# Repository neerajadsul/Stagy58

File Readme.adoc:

= Ortho82Split Keyboard
This is the current design iteration which has 41 keys on each half in orthogonal matrix.

KiCAD 7 Render

image::images/Ortho82SplitLeftHalf.jpg[]

Fully assembled two halves of the keyboard, side by side

image::images/FullyAssembledLeftRight.jpg[]

== Programmers Model

=== Row Signals to Microcontroller Pin

[cols="1,1,1"]
|===
| Signal | Pin | Keyboard Row

|ROW_F | PD0 | Esc, Function row
|ROW_0 | PD1 | Backtick, Numbers row
|ROW_1 | PD2 | Tab, QWERTY row
|ROW_2 | PD3 | Caps, ASDFG row
|ROW_3 | PD4 | Shift, ZXCVB row
|ROW_4 | PD5 | Ctrl, Fn, Opt, Cmd, Space row
|===

=== Column Signals to Microcontroller Pin
==== Left Half of the Split Keyboard
[cols="s,1,1,1,1,1,1,1"]
|===
|Signal | COL_0 | COL_1  | COL_2 | COL_3 | COL_4 | COL_5  | COL_6

| Pin | PC0 | PC1 | PC2 | PC3 | PC4 | PC5 | PC6 

|ROW_F | Esc | F1 | F2 | F3 | F4 | F5 | F6
|ROW_0 | ` (backtick) | 1 | 2 | 3 | 4 | 5 | 6
|ROW_1 | Tab | Q | W | E | R | T | Y
|ROW_2 | Caps | A | S | D | F | G | H
|ROW_3 | Shift | \ (backslash) | Z | X | C | V | B 
|ROW_4 | <NO KEY> | Ctrl  | MOD | Fn | Option | Cmd | Space | 
|===

==== Right Half of the Split Keyboard
[cols="s,1,1,1,1,1,1,1"]
|===
| Signal | COL_6 | COL_5  | COL_4 | COL_3 | COL_2 | COL_1  | COL_0
| Pin | PC6 | PC5 | PC4 | PC3 | PC2 | PC1 | PC0 

|ROW_F | F7 | F8 | F9 | F10 | F11 | F12 | Del
|ROW_0 | 7 | 8 | 9 | 0 | - | = | Backspace
|ROW_1 | U | I | O | P | [ | ] | Enter
|ROW_2 | J | K | L | ;: | '@ (quote) | # | Enter
|ROW_3 | N | M | ,< | .> | /? | UP | SHIFT 
|ROW_4 | Space | Cmd  | Option | LEFT | DOWN | RIGHT | <No Key> | 
|===

=== Communication between Left and Right Halves
Two halves of the split keyboard are connected by USART connection.
[cols="s,1,1"]
|===
| Signal | RXD0 | TXD0
| Pin | PE2 | PE3 
|===

=== Left/Right Half Identification and Indicator LED
Left and right are identified by setting a solder jumper on the board.
Left is 0 and right is 1.

[cols="s,1,1"]
|===
| Signal | Left-Right | Indicator LED
| Pin | PB2 | PB3 
|===

== Iterative Design History
I started with my TKL (tenkeyless) keyboard and tried to reduce the keys. 
I managed to reduce to 60 = 58 main + 2 extended keys for the keyboard.
This was partially inspired by Lily58 and other 60% keyboards avaialble. 
Also Kyria keyboard inspired me to customise the positions of the keys 
adapted to my hands and fingers. 
Following ficgure shows how I came up with draft with reduction in keys 
and logical positions in a worksheet. 

image::images/keys_reduction.png[]

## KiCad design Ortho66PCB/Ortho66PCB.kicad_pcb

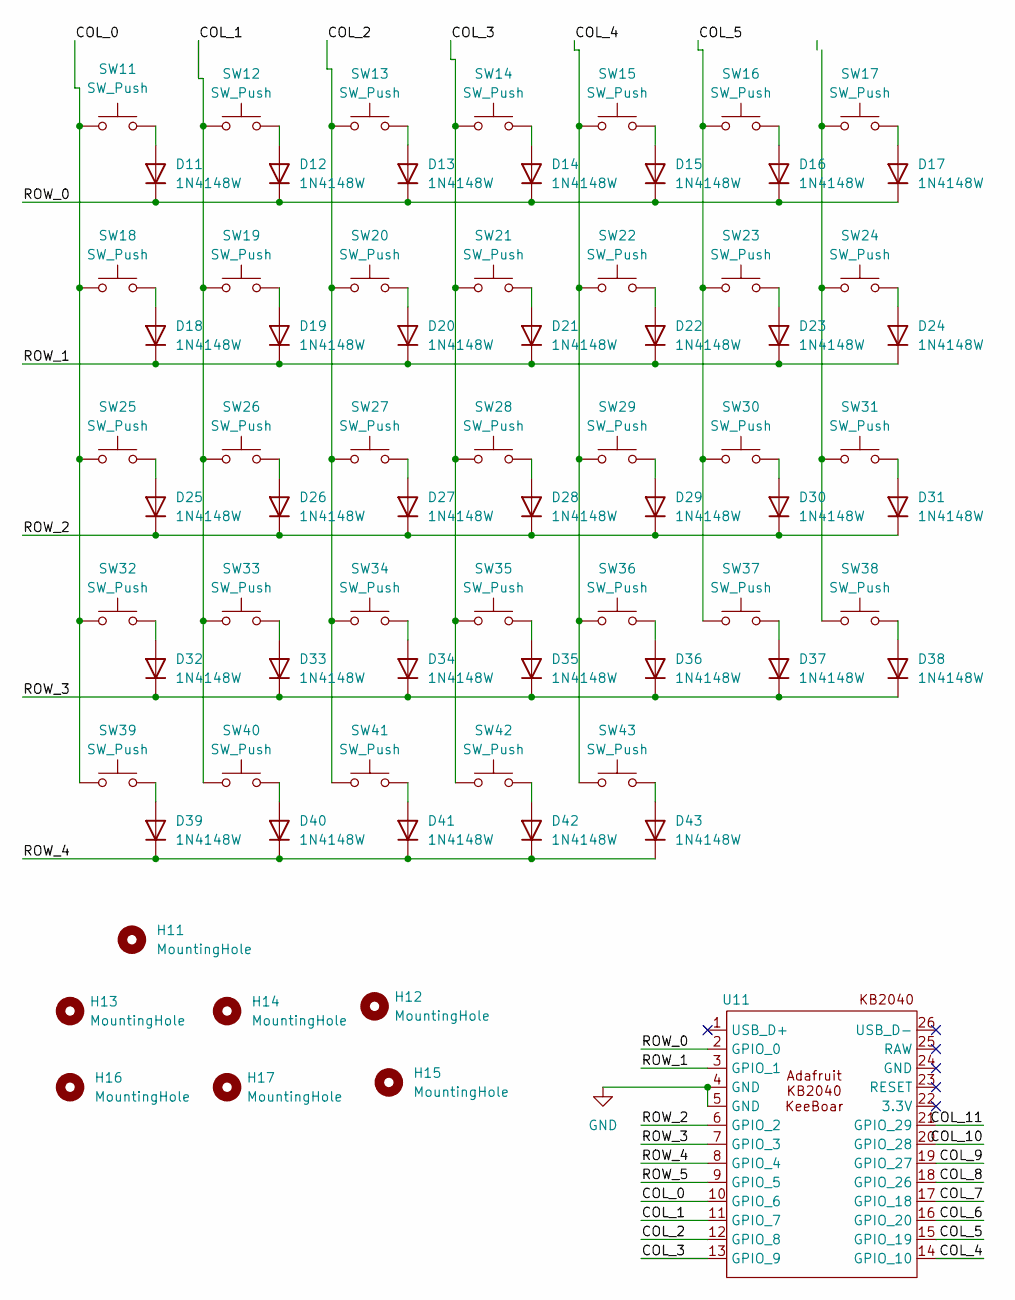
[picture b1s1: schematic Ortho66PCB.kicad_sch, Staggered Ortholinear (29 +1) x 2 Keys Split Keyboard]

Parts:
D11, D12, D13, D14, D15, D16, D17, D18, D19, D20, D21, D22, D23, D24, D25, D26, D27, D28, D29, D30, D31, D32, D33, D34, D35, D36, D37, D38, D39, D40, D41, D42, D43: 1N4148W; D_SOD-123
H11: MountingHole; MountingHole_2.7mm_M2.5
H12, H13, H14, H15, H16, H17: MountingHole; MountingHole_3.2mm_M3
SW11, SW18, SW25, SW32: SW_Push; SW_Kailh_Choc_V1V2_1.50u
SW12, SW13, SW14, SW15, SW16, SW17, SW19, SW20, SW21, SW22, SW23, SW24, SW26, SW27, SW28, SW29, SW30, SW31, SW33, SW34, SW35, SW36, SW37, SW38, SW39, SW40, SW42, SW43: SW_Push; SW_Kailh_Choc_V1V2_1.00u
SW41: SW_Push; SW_Kailh_Choc_V1V2_2.00u
U11: KB2040

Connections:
/COL_0: SW11.1, SW18.1, SW25.1, SW32.1, SW39.1, U11.10 (GPIO_6)
/COL_1: SW12.1, SW19.1, SW26.1, SW33.1, SW40.1, U11.11 (GPIO_7)
/COL_2: SW13.1, SW20.1, SW27.1, SW34.1, SW41.1, U11.12 (GPIO_8)
/COL_3: SW14.1, SW21.1, SW28.1, SW35.1, SW42.1, U11.13 (GPIO_9)
/COL_4: SW15.1, SW22.1, SW29.1, SW36.1, SW43.1, U11.14 (GPIO_10)
/COL_5: SW16.1, SW23.1, SW30.1, SW37.1, U11.15 (GPIO_19)
/COL_6: U11.16 (GPIO_20)
/COL_7: U11.17 (GPIO_18)
/COL_8: U11.18 (GPIO_26)
/COL_9: U11.19 (GPIO_27)
/COL_10: U11.20 (GPIO_28)
/COL_11: U11.21 (GPIO_29)
/ROW_0: D11.1 (K), D12.1 (K), D13.1 (K), D14.1 (K), D15.1 (K), D16.1 (K), D17.1 (K), U11.2 (GPIO_0)
/ROW_1: D18.1 (K), D19.1 (K), D20.1 (K), D21.1 (K), D22.1 (K), D23.1 (K), D24.1 (K), U11.3 (GPIO_1)
/ROW_2: D25.1 (K), D26.1 (K), D27.1 (K), D28.1 (K), D29.1 (K), D30.1 (K), D31.1 (K), U11.6 (GPIO_2)
/ROW_3: D32.1 (K), D33.1 (K), D34.1 (K), D35.1 (K), D36.1 (K), D37.1 (K), D38.1 (K), U11.7 (GPIO_3)
/ROW_4: D39.1 (K), D40.1 (K), D41.1 (K), D42.1 (K), D43.1 (K), U11.8 (GPIO_4)
/ROW_5: U11.9 (GPIO_5)
GND: U11.4 (GND), U11.5 (GND)
unnamed: D11.2 (A), SW11.2
unnamed: D12.2 (A), SW12.2
unnamed: D13.2 (A), SW13.2
unnamed: D14.2 (A), SW14.2
unnamed: D15.2 (A), SW15.2
unnamed: D16.2 (A), SW16.2
unnamed: D17.2 (A), SW17.2
unnamed: D18.2 (A), SW18.2
unnamed: D19.2 (A), SW19.2
unnamed: D20.2 (A), SW20.2
unnamed: D21.2 (A), SW21.2
unnamed: D22.2 (A), SW22.2
unnamed: D23.2 (A), SW23.2
unnamed: D24.2 (A), SW24.2
unnamed: D25.2 (A), SW25.2
unnamed: D26.2 (A), SW26.2
unnamed: D27.2 (A), SW27.2
unnamed: D28.2 (A), SW28.2
unnamed: D29.2 (A), SW29.2
unnamed: D30.2 (A), SW30.2
unnamed: D31.2 (A), SW31.2
unnamed: D32.2 (A), SW32.2
unnamed: D33.2 (A), SW33.2
unnamed: D34.2 (A), SW34.2
unnamed: D35.2 (A), SW35.2
unnamed: D36.2 (A), SW36.2
unnamed: D37.2 (A), SW37.2
unnamed: D38.2 (A), SW38.2
unnamed: D39.2 (A), SW39.2
unnamed: D40.2 (A), SW40.2
unnamed: D41.2 (A), SW41.2
unnamed: D42.2 (A), SW42.2
unnamed: D43.2 (A), SW43.2
unnamed: SW17.1, SW24.1, SW31.1, SW38.1

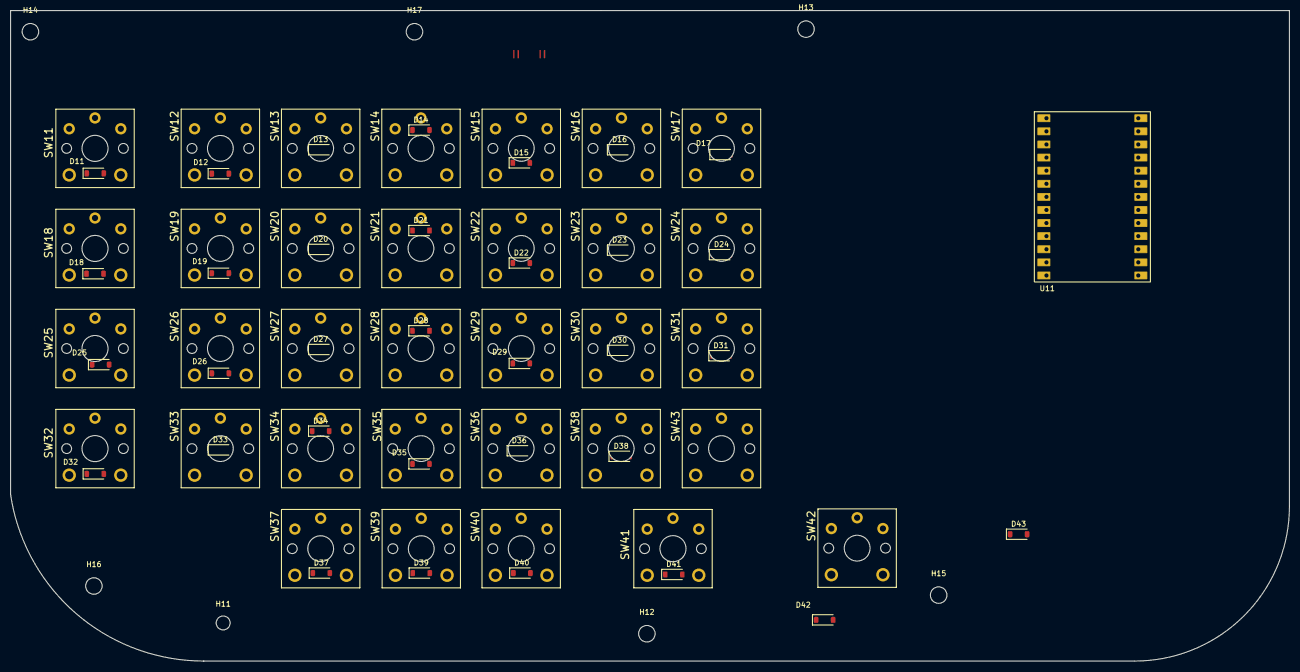
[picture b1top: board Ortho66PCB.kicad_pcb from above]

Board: 2 copper layers, 247.9 x 126.1 mm, 74 parts (0 on the bottom side), 46 nets.

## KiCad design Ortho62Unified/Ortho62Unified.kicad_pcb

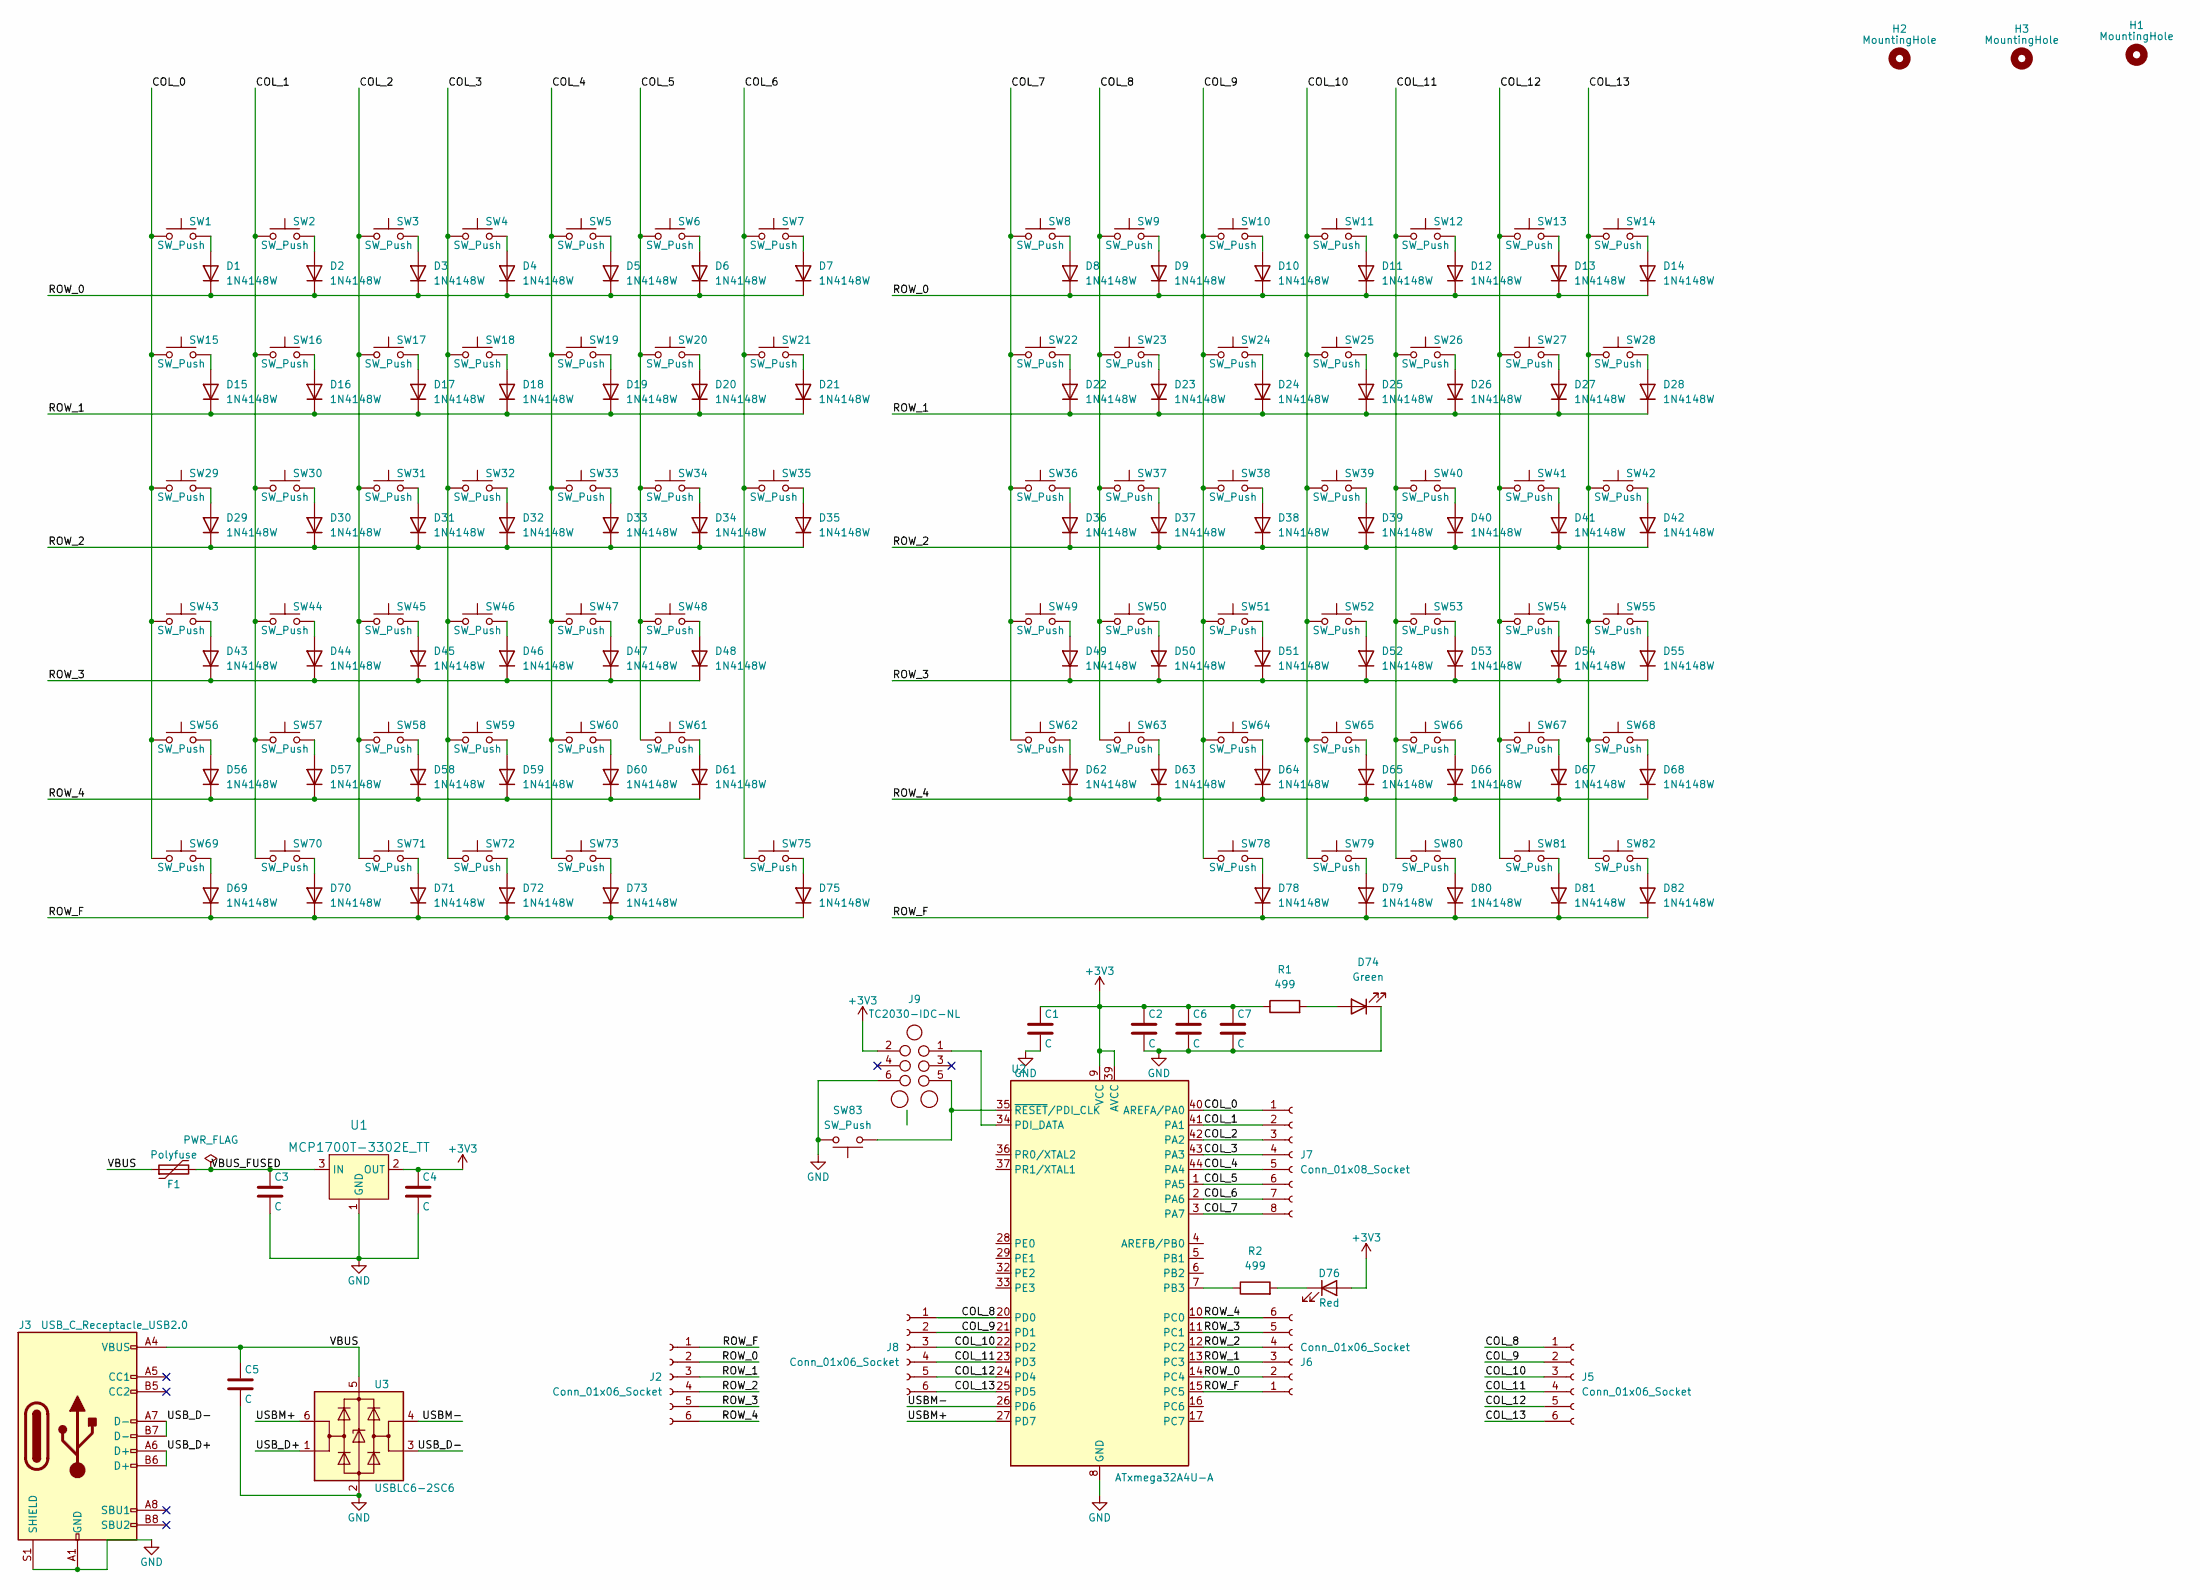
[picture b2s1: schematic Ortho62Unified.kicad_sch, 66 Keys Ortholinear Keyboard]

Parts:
C1, C2, C3, C4, C5, C6, C7: C; C_0603_1608Metric_Pad1.08x0.95mm_HandSolder
D1, D2, D3, D4, D5, D6, D7, D8, D9, D10, D11, D12, D13, D14, D15, D16, D17, D18, D19, D20, D21, D22, D23, D24, D25, D26, D27, D28, D29, D30, D31, D32, D33, D34, D35, D36, D37, D38, D39, D40, D41, D42, D43, D44, D45, D46, D47, D48, D49, D50, D51, D52, D53, D54, D55, D56, D57, D58, D59, D60, D61, D62, D63, D64, D65, D66, D67, D68, D69, D70, D71, D72, D73, D75, D78, D79, D80, D81, D82: 1N4148W; D_SOD-123
D74: Green; LED_0805_2012Metric_Pad1.15x1.40mm_HandSolder
D76: Red; LED_0805_2012Metric_Pad1.15x1.40mm_HandSolder
F1: Polyfuse; Fuse_1206_3216Metric_Pad1.42x1.75mm_HandSolder
H1, H2, H3: MountingHole; MountingHole_3.2mm_M3
J2, J5, J6, J8: Conn_01x06_Socket; PinHeader_1x06_P1.27mm_Vertical
J3: USB_C_Receptacle_USB2.0; USB_C_Receptacle_GCT_USB4085_HandSolder_SMT
J7: Conn_01x08_Socket; PinHeader_1x08_P1.27mm_Vertical
J9: TC2030-IDC-NL
R1: 499; R_0805_2012Metric_Pad1.20x1.40mm_HandSolder
R2: 499; LED_0805_2012Metric_Pad1.15x1.40mm_HandSolder
SW1, SW2, SW3, SW4, SW5, SW6, SW8, SW9, SW10, SW11, SW12, SW13, SW15, SW16, SW17, SW18, SW19, SW20, SW22, SW23, SW24, SW25, SW26, SW27, SW29, SW30, SW31, SW32, SW33, SW34, SW36, SW37, SW38, SW39, SW40, SW41, SW43, SW44, SW45, SW46, SW47, SW48, SW49, SW50, SW51, SW52, SW53, SW54, SW55, SW57, SW58, SW59, SW60, SW63, SW64, SW65, SW66, SW68, SW69, SW70, SW71, SW72, SW73, SW78, SW79, SW80, SW81: SW_Push; SW_Kailh_Choc_V1V2_1.00u
SW7, SW14, SW21, SW28, SW35, SW42, SW56, SW61, SW62, SW67, SW75, SW82: SW_Push; SW_Kailh_Choc_V1V2_1.50u
SW83: SW_Push; SW_Tactile_SPST_NO_Straight_CK_PTS636Sx25SMTRLFS
U1: MCP1700T-3302E_TT; SOT-23-3; MPN MCP1700T-3302E/TT; Digi-Key_PN MCP1700T3302ETTCT-ND
U2: ATxmega32A4U-A; TQFP-44_10x10mm_P0.8mm
U3: USBLC6-2SC6; SOT-23-6

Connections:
+3V3: C1.1, C2.1, C4.1, C6.1, C7.1, D76.2 (A), J9.2, R1.1, U1.2 (OUT), U2.9 (VCC), U2.19 (VCC), U2.31 (VCC), U2.39 (AVCC)
/COL_0: J7.1, SW1.1, SW15.1, SW29.1, SW43.1, SW56.1, SW69.1, U2.40 (AREFA/PA0)
/COL_1: J7.2, SW2.1, SW16.1, SW30.1, SW44.1, SW57.1, SW70.1, U2.41 (PA1)
/COL_2: J7.3, SW3.1, SW17.1, SW31.1, SW45.1, SW58.1, SW71.1, U2.42 (PA2)
/COL_3: J7.4, SW4.1, SW18.1, SW32.1, SW46.1, SW59.1, SW72.1, U2.43 (PA3)
/COL_4: J7.5, SW5.1, SW19.1, SW33.1, SW47.1, SW60.1, SW73.1, U2.44 (PA4)
/COL_5: J7.6, SW6.1, SW20.1, SW34.1, SW48.1, SW61.1, U2.1 (PA5)
/COL_6: J7.7, SW7.1, SW21.1, SW35.1, SW75.1, U2.2 (PA6)
/COL_7: J7.8, SW8.1, SW22.1, SW36.1, SW49.1, SW62.1, U2.3 (PA7)
/COL_8: J5.1, J8.1, SW9.1, SW23.1, SW37.1, SW50.1, SW63.1, U2.20 (PD0)
/COL_9: J5.2, J8.2, SW10.1, SW24.1, SW38.1, SW51.1, SW64.1, SW78.1, U2.21 (PD1)
/COL_10: J5.3, J8.3, SW11.1, SW25.1, SW39.1, SW52.1, SW65.1, SW79.1, U2.22 (PD2)
/COL_11: J5.4, J8.4, SW12.1, SW26.1, SW40.1, SW53.1, SW66.1, SW80.1, U2.23 (PD3)
/COL_12: J5.5, J8.5, SW13.1, SW27.1, SW41.1, SW54.1, SW67.1, SW81.1, U2.24 (PD4)
/COL_13: J5.6, J8.6, SW14.1, SW28.1, SW42.1, SW55.1, SW68.1, SW82.1, U2.25 (PD5)
/ROW_0: D1.1 (K), D2.1 (K), D3.1 (K), D4.1 (K), D5.1 (K), D6.1 (K), D7.1 (K), D8.1 (K), D9.1 (K), D10.1 (K), D11.1 (K), D12.1 (K), D13.1 (K), D14.1 (K), J2.2, J6.2, U2.14 (PC4)
/ROW_1: D15.1 (K), D16.1 (K), D17.1 (K), D18.1 (K), D19.1 (K), D20.1 (K), D21.1 (K), D22.1 (K), D23.1 (K), D24.1 (K), D25.1 (K), D26.1 (K), D27.1 (K), D28.1 (K), J2.3, J6.3, U2.13 (PC3)
/ROW_2: D29.1 (K), D30.1 (K), D31.1 (K), D32.1 (K), D33.1 (K), D34.1 (K), D35.1 (K), D36.1 (K), D37.1 (K), D38.1 (K), D39.1 (K), D40.1 (K), D41.1 (K), D42.1 (K), J2.4, J6.4, U2.12 (PC2)
/ROW_3: D43.1 (K), D44.1 (K), D45.1 (K), D46.1 (K), D47.1 (K), D48.1 (K), D49.1 (K), D50.1 (K), D51.1 (K), D52.1 (K), D53.1 (K), D54.1 (K), D55.1 (K), J2.5, J6.5, U2.11 (PC1)
/ROW_4: D56.1 (K), D57.1 (K), D58.1 (K), D59.1 (K), D60.1 (K), D61.1 (K), D62.1 (K), D63.1 (K), D64.1 (K), D65.1 (K), D66.1 (K), D67.1 (K), D68.1 (K), J2.6, J6.6, U2.10 (PC0)
/ROW_F: D69.1 (K), D70.1 (K), D71.1 (K), D72.1 (K), D73.1 (K), D75.1 (K), D78.1 (K), D79.1 (K), D80.1 (K), D81.1 (K), D82.1 (K), J2.1, J6.1, U2.15 (PC5)
/USBM+: U2.27 (PD7), U3.6 (I/O1)
/USBM-: U2.26 (PD6), U3.4 (I/O2)
/USB_D+: J3.A6 (D+), J3.B6 (D+), U3.1 (I/O1)
/USB_D-: J3.A7 (D-), J3.B7 (D-), U3.3 (I/O2)
/VBUS: C5.1, F1.1, J3.A4 (VBUS), J3.A9 (VBUS), J3.B4 (VBUS), J3.B9 (VBUS), U3.5 (VBUS)
/VBUS_FUSED: C3.1, F1.2, U1.3 (IN)
GND: C1.2, C2.2, C3.2, C4.2, C5.2, C6.2, C7.2, D74.1 (K), J3.A1 (GND), J3.A12 (GND), J3.B1 (GND), J3.B12 (GND), J3.S1 (SHIELD), J9.6, SW83.2, U1.1 (GND), U2.8 (GND), U2.18 (GND), U2.30 (GND), U2.38 (GND), U3.2 (GND)
unnamed: D1.2 (A), SW1.2
unnamed: D2.2 (A), SW2.2
unnamed: D3.2 (A), SW3.2
unnamed: D4.2 (A), SW4.2
unnamed: D5.2 (A), SW5.2
unnamed: D6.2 (A), SW6.2
unnamed: D7.2 (A), SW7.2
unnamed: D8.2 (A), SW8.2
unnamed: D9.2 (A), SW9.2
unnamed: D10.2 (A), SW10.2
unnamed: D11.2 (A), SW11.2
unnamed: D12.2 (A), SW12.2
unnamed: D13.2 (A), SW13.2
unnamed: D14.2 (A), SW14.2
unnamed: D15.2 (A), SW15.2
unnamed: D16.2 (A), SW16.2
unnamed: D17.2 (A), SW17.2
unnamed: D18.2 (A), SW18.2
unnamed: D19.2 (A), SW19.2
unnamed: D20.2 (A), SW20.2
unnamed: D21.2 (A), SW21.2
unnamed: D22.2 (A), SW22.2
unnamed: D23.2 (A), SW23.2
unnamed: D24.2 (A), SW24.2
unnamed: D25.2 (A), SW25.2
unnamed: D26.2 (A), SW26.2
unnamed: D27.2 (A), SW27.2
unnamed: D28.2 (A), SW28.2
unnamed: D29.2 (A), SW29.2
unnamed: D30.2 (A), SW30.2
unnamed: D31.2 (A), SW31.2
unnamed: D32.2 (A), SW32.2
unnamed: D33.2 (A), SW33.2
unnamed: D34.2 (A), SW34.2
unnamed: D35.2 (A), SW35.2
unnamed: D36.2 (A), SW36.2
unnamed: D37.2 (A), SW37.2
unnamed: D38.2 (A), SW38.2
unnamed: D39.2 (A), SW39.2
unnamed: D40.2 (A), SW40.2
unnamed: D41.2 (A), SW41.2
unnamed: D42.2 (A), SW42.2
unnamed: D43.2 (A), SW43.2
unnamed: D44.2 (A), SW44.2
unnamed: D45.2 (A), SW45.2
unnamed: D46.2 (A), SW46.2
unnamed: D47.2 (A), SW47.2
unnamed: D48.2 (A), SW48.2
unnamed: D49.2 (A), SW49.2
unnamed: D50.2 (A), SW50.2
unnamed: D51.2 (A), SW51.2
unnamed: D52.2 (A), SW52.2
unnamed: D53.2 (A), SW53.2
unnamed: D54.2 (A), SW54.2
unnamed: D55.2 (A), SW55.2
unnamed: D56.2 (A), SW56.2
unnamed: D57.2 (A), SW57.2
unnamed: D58.2 (A), SW58.2
unnamed: D59.2 (A), SW59.2
unnamed: D60.2 (A), SW60.2
unnamed: D61.2 (A), SW61.2
unnamed: D62.2 (A), SW62.2
unnamed: D63.2 (A), SW63.2
unnamed: D64.2 (A), SW64.2
unnamed: D65.2 (A), SW65.2
unnamed: D66.2 (A), SW66.2
unnamed: D67.2 (A), SW67.2
unnamed: D68.2 (A), SW68.2
unnamed: D69.2 (A), SW69.2
unnamed: D70.2 (A), SW70.2
unnamed: D71.2 (A), SW71.2
unnamed: D72.2 (A), SW72.2
unnamed: D73.2 (A), SW73.2
unnamed: D74.2 (A), R1.2
unnamed: D75.2 (A), SW75.2
unnamed: D76.1 (K), R2.2
unnamed: D78.2 (A), SW78.2
unnamed: D79.2 (A), SW79.2
unnamed: D80.2 (A), SW80.2
unnamed: D81.2 (A), SW81.2
unnamed: D82.2 (A), SW82.2
unnamed: J9.1, U2.34 (PDI_DATA)
unnamed: J9.5, SW83.1, U2.35 (~RESET/PDI_CLK)
unnamed: R2.1, U2.7 (PB3)

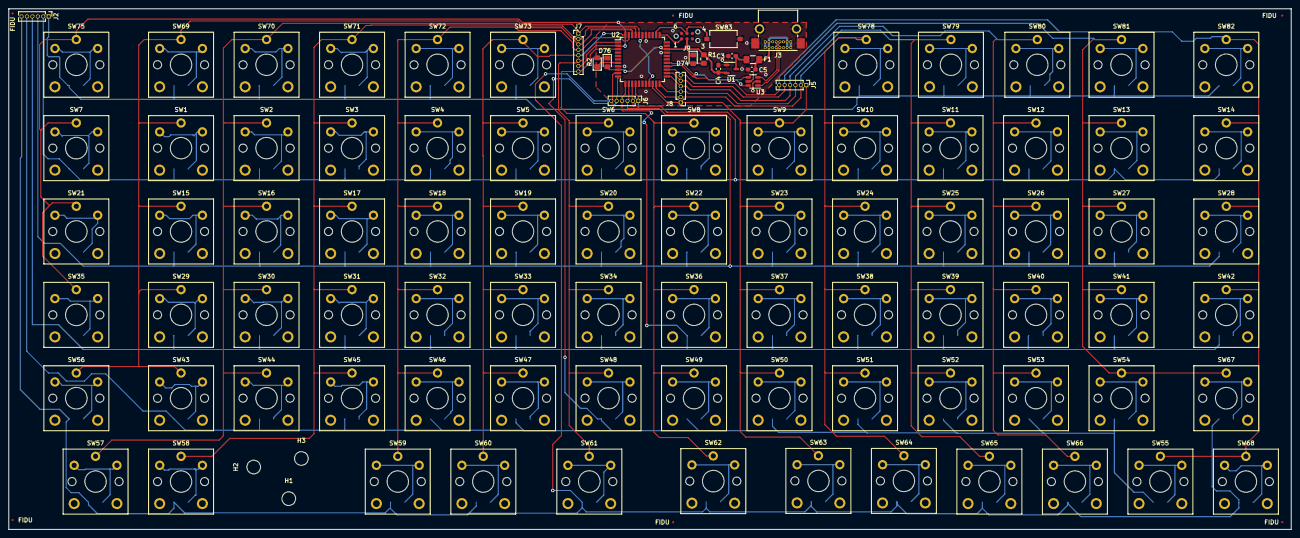
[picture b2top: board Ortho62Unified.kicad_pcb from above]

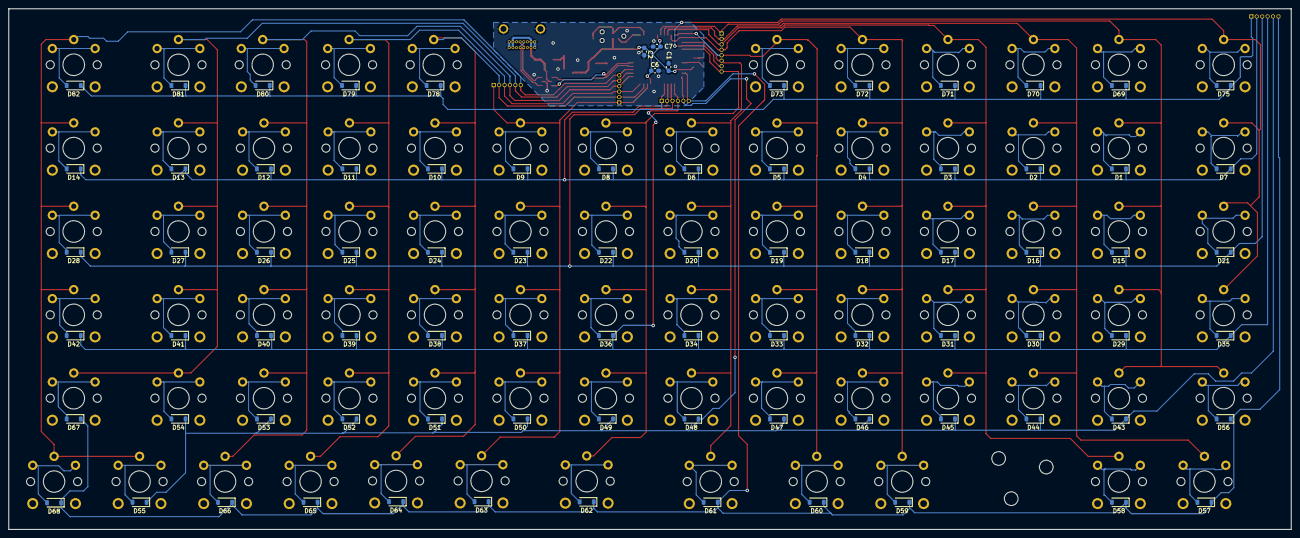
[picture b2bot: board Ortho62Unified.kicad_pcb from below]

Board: 2 copper layers, 300.0 x 121.8 mm, 190 parts (83 on the bottom side), 112 nets.

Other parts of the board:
FIDU: Fiducial_0.5mm_Mask1mm
FIDU#2, FIDU#3, FIDU#4, FIDU#5, FIDU#6: Fiducial_0.5mm_Mask1mm

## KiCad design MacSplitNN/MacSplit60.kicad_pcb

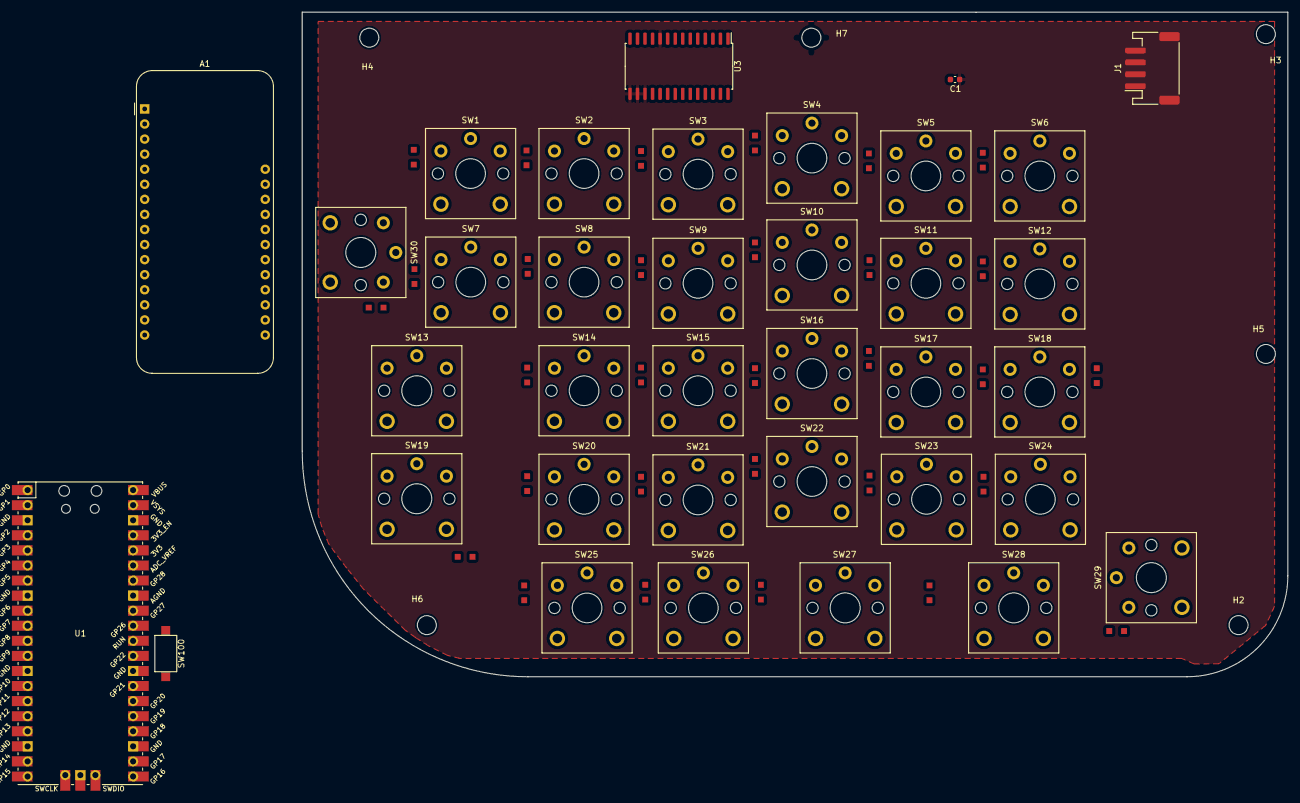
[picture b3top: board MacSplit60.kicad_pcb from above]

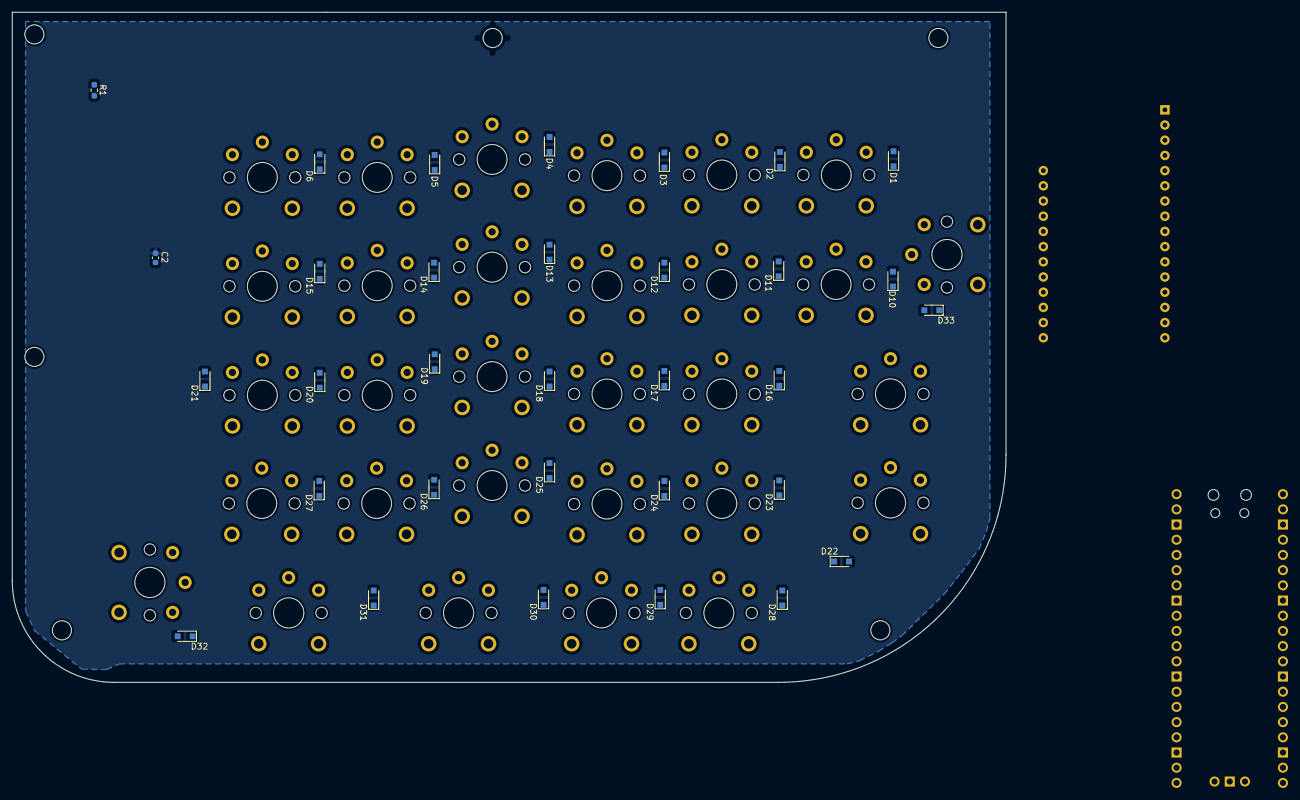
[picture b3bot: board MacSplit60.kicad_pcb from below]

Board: 2 copper layers, 166.1 x 112.0 mm, 74 parts (32 on the bottom side), 47 nets, no tracks yet.

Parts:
A1: Adafruit_Feather_Generic; Adafruit_Feather
C1, C2: C; C_0603_1608Metric
D1, D2, D3, D4, D5, D6, D10, D11, D12, D13, D14, D15, D16, D17, D18, D19, D20, D21, D22, D23, D24, D25, D26, D27, D28, D29, D30, D31, D32, D33: 1N4148W; D_SOD-323_Hand_Split_Keyboard
H2, H3, H4, H5, H6, H7: MountingHole; MountingHole_3.2mm_M3
J1: Conn_01x04_Pin; JST_PH_S4B-PH-SM4-TB_1x04-1MP_P2.00mm_Horizontal
R1: 0; R_0603_1608Metric_Pad0.98x0.95mm_HandSolder
SW1, SW2, SW3, SW4, SW5, SW6, SW7, SW8, SW9, SW10, SW11, SW12, SW14, SW15, SW16, SW17, SW18, SW20, SW21, SW22, SW23, SW24, SW25, SW26: SW_Push; SW_Kailh_Choc_V1V2_1.00u
SW13, SW19: SW_Push; SW_Kailh_Choc_V1V2_2.00u
SW27, SW28, SW29, SW30: SW_Push; SW_Kailh_Choc_V1V2_1.50u
SW100: SW_SPST; SW_SPST_CK_RS282G05A3
U1: Pico; RPi_Pico_SMD_TH
U3: MCP23017_SO; SOIC-28W_7.5x17.9mm_P1.27mm

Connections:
+VDC: C1.1, C2.1, J1.1, R1.2, U3.9 (VDD), U3.18 (~RESET)
/COL_0: SW1.1, SW7.1, SW13.1, SW19.1, SW25.1, U1.29 (GPIO22), U3.21 (GPA0)
/COL_1: SW2.1, SW8.1, SW14.1, SW20.1, SW26.1, U1.27 (GPIO21), U3.22 (GPA1)
/COL_2: SW3.1, SW9.1, SW15.1, SW21.1, SW27.1, U1.26 (GPIO20), U3.23 (GPA2)
/COL_3: SW4.1, SW10.1, SW16.1, SW22.1, SW28.1, U1.25 (GPIO19), U3.24 (GPA3)
/COL_4: SW5.1, SW11.1, SW17.1, SW23.1, SW29.1, U1.24 (GPIO18), U3.25 (GPA4)
/COL_5: SW6.1, SW12.1, SW18.1, SW24.1, SW30.1, U1.22 (GPIO17), U3.26 (GPA5)
/ROW_0: D1.1 (K), D2.1 (K), D3.1 (K), D4.1 (K), D5.1 (K), D6.1 (K), U1.21 (GPIO16), U3.1 (GPB0)
/ROW_1: D10.1 (K), D11.1 (K), D12.1 (K), D13.1 (K), D14.1 (K), D15.1 (K), U1.20 (GPIO15), U3.2 (GPB1)
/ROW_2: D16.1 (K), D17.1 (K), D18.1 (K), D19.1 (K), D20.1 (K), D21.1 (K), U1.19 (GPIO14), U3.3 (GPB2)
/ROW_3: D22.1 (K), D23.1 (K), D24.1 (K), D25.1 (K), D26.1 (K), D27.1 (K), U1.17 (GPIO13), U3.4 (GPB3)
/ROW_4: D28.1 (K), D29.1 (K), D30.1 (K), D31.1 (K), D32.1 (K), D33.1 (K), U1.16 (GPIO12), U3.5 (GPB4)
/SCL_IOEXP: J1.3, U1.5 (GPIO3), U3.12 (SCK)
/SDA_IOEXP: J1.2, U1.4 (GPIO2), U3.13 (SDA)
GND: C1.2, C2.2, J1.4, SW100.2 (B), U1.3 (GND), U1.8 (GND), U1.13 (GND), U1.18 (GND), U1.23 (GND), U1.28 (GND), U3.10 (VSS), U3.15 (A0), U3.16 (A1), U3.17 (A2)
unnamed: D1.2 (A), SW1.2
unnamed: D2.2 (A), SW2.2
unnamed: D3.2 (A), SW3.2
unnamed: D4.2 (A), SW4.2
unnamed: D5.2 (A), SW5.2
unnamed: D6.2 (A), SW6.2
unnamed: D10.2 (A), SW7.2
unnamed: D11.2 (A), SW8.2
unnamed: D12.2 (A), SW9.2
unnamed: D13.2 (A), SW10.2
unnamed: D14.2 (A), SW11.2
unnamed: D15.2 (A), SW12.2
unnamed: D16.2 (A), SW13.2
unnamed: D17.2 (A), SW14.2
unnamed: D18.2 (A), SW15.2
unnamed: D19.2 (A), SW16.2
unnamed: D20.2 (A), SW17.2
unnamed: D21.2 (A), SW18.2
unnamed: D22.2 (A), SW19.2
unnamed: D23.2 (A), SW20.2
unnamed: D24.2 (A), SW21.2
unnamed: D25.2 (A), SW22.2
unnamed: D26.2 (A), SW23.2
unnamed: D27.2 (A), SW24.2
unnamed: D28.2 (A), SW25.2
unnamed: D29.2 (A), SW26.2
unnamed: D30.2 (A), SW27.2
unnamed: D31.2 (A), SW28.2
unnamed: D32.2 (A), SW29.2
unnamed: D33.2 (A), SW30.2
unnamed: SW100.1 (A), U1.30 (RUN)
unnamed: R1.1, U1.36 (3V3)

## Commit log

2022-12-31 Blank Project
2022-12-31 30 push-button switches in schematic
2022-12-31 Creates readme file for design record
2022-12-31 Key switches matrix 6x5 with diodes
2023-01-02 Adds ports expander and USB-C for split bridge
2023-01-02 Assigns inner 4x4 switches 1u footprints
2023-01-02 Assigns Ctrl, Cmd, Alt switches 1.25u footprints
2023-01-02 Working draft for key positions
2023-01-03 Comfortable positions of the keys, ready to layout
2023-01-03 Placed all components, board outline added
2023-01-03 Partial routing complete, approx 40%
2023-01-04 Routes rows, columns in switches
2023-01-04 Completes routing of the board
2023-01-05 updated 58 keys layout
2023-01-05 Updated placement for switches as per MacSplit60
2023-01-05 Design layout documentation
2023-01-05 Updates summary of the switches
2023-01-05 Updates the license
2023-01-05 Updates switches positions according to MacSplit60 layout
2023-01-05 Corrects the PCB edge
2023-01-05 Equalises and checks switches spacing, diodes on both layers
2023-01-05 Completes routing of the PCB
2023-01-05 Generates interactive BOM
2023-01-06 Adds PCB design info to silkscreen, gerbers for production
2023-01-09 Changes USB-C footprint to circular hole and pad
2023-01-10 simple rectangular block for USB-C connector
2023-01-10 Updates logic for reduction of keys from 79 to 60.
2023-01-10 Updates keyboard image with correct 3dModel for switch
2023-01-13 Performs single keypress test
2023-01-19 Scans 30 keys matrix, left side of split
2023-01-22 working keyboard along with the required libs
2023-01-22 comments keycodes, mod key backspace, arrows, quotes, backtick,tilda
2023-01-22 updates layout
2023-01-22 Updates docs
2023-02-03 swap backspace and backslash
2023-02-03 Adafruit KB2040 board symbol and footprint
2023-02-03 Modify switches footprints, TRRS board to board
2023-02-03 remove all vias, tracks
2023-02-03 Adds CherryMX footprints with safe keycap border
2023-02-03 Update footprint, start repositioning keys
2023-02-05 ignores temporary files
2023-02-07 Aligns rows and columns of switches
2023-02-07 Starting left side of the keyboard
2023-02-07 Left 32 keys
2023-02-26 Position readjustments
2023-02-26 Prepare for unified ortholinear keyboard
2023-02-26 66 keys placed in a grid
2023-02-26 Keeps 1u, 1.5u and 2u footprints, removes everything else
2023-02-27 66 keys in grid
2023-07-07 Add row-wise key placement docs
2023-07-07 Connections for grid layout keys.
2023-07-07 Update symbol and footprint table.
2023-07-07 Update layout image and json for reference.
2023-07-07 Save files in KiCad version 7 format.
2023-07-07 Rearrange keys, add AVR micro.
2023-07-10 66 symmetrical layout.
2023-07-10 Add cutout border for 3D visualisation
2023-07-12 Draft update - remove USB-C and IO Expander chip, unroute all.
2023-07-12 Align and correctly space 66 keys.
2023-07-13 Add function keys row.
2023-07-13 Place and align all 82 keys.
2023-07-13 Place all diodes within keys.
2023-07-13 Route rows and colums of keyboard matrix to 1.27mm headers.
2023-07-13 Project file format to V7.
2023-07-13 Consolitate and place Xmega and USB components.
2023-07-14 Remove F6,F7,F8 keys to create space for controller.
2023-07-14 Progress routing rows and columns.
2023-07-15 First commit with working configuration.
2023-07-17 Simple test using Ortho62 keyboard hardware.
2023-07-17 Routing complete for Xmega based design.
2023-07-18 STM32 L0 CubeMX generated project code.
2023-07-18 Set column output mode to Push-Pull and read rows.
2023-07-18 USB device descriptor enumration fails.
2023-07-18 Holding keypress works with usb_putbuf function.
2023-07-18 Functioning USB HID Keyboard interface with Linux, macOS and Windows.
2023-07-19 Add fiducials on PCB.
2023-07-19 Add no-net copper across entire board.
2023-07-19 Add additional key in bottom row.
2023-07-19 Makes bottom row with modifier keys symmetric.
2023-07-19 Draft left half of split-keyboard.
2023-07-20 Corrects spacing between keyswitches.
2023-07-20 Route USB and xmega circuit.
2023-07-20 Routing complete.
2023-07-20 Adds USB current resistors.
2023-07-21 Adds reference footprints in empty space.
2023-07-21 Add 125 systems and KiCad Logos.
2023-07-21 Add interative bill-of-materials for the ordered revision.
2023-07-21 Remove temporary file that was commited by mistake.
2023-08-04 Update documentation for programmers model, add 3D render.
2023-08-04 Document and tidyup schematic.
2023-08-04 Update interactive BOM and export schematic pdf for reference.
2023-08-06 VSCode settings for AVR-GCC plugin.
2023-08-06 Ignore build folder.
2023-08-06 Create skeleton of the firmware.
2023-08-06 Check oscillator ready, Red LED On on startup.
2023-08-06 LED blinking
2023-08-06 Working USARTE0, system clock is still 2MHz internal.
2023-08-07 Refactor to start developing Keypad scan.
2023-08-07 All in one file.
2023-08-07 USB device descriptors and enumerators.
2023-08-08 Add keyboard scan map.
2023-08-08 Updated project file.
2023-08-08 Update documentation on schematic and PCB.
2023-08-08 Pull-down PORTC to get zero when no key is pressed.
2023-08-08 Correct the kay mapping.
2023-08-08 Remove unused code.
2023-08-08 Add feature to display keyboard scan map linking matrix to real keymap.
2023-08-08 Correct right half scan map and send left or right configuration from main function.
2023-08-09 Working key presses except for GUI key.
2023-08-09 Current state.
2023-08-09 Fresh USB HID Keyboard with interrupt driven approach.
2023-08-09 Ignore build files and remove tracked project filed commited by mistake.
2023-08-09 Clean up main to remove unused code.
2023-08-09 Define useful bitmasks for row and column and macro for row signal readout.
2023-08-09 Provide printing of row, column and key name for easy debug.
2023-08-10 Restructure for clarity and being able to detect press-down, release of a key.
2023-08-10 Logic clean up.
2023-08-10 Reformat to reduce horizontal indentation.
2023-08-10 Better logic for key scanning and debouncing.
2023-08-10 Simplify switch case.
2023-08-10 Correct modifier logic, detect modifiers and regular keys.
2023-08-10 Remove unused code, clean up.
2023-08-10 Final tryout, does not work, I give up with CodevisionAVR.
2023-08-11 Ignore vscode generated files.
2023-08-11 Documentation update with photos of assembled keyboard.
2023-08-11 Correct the formatting.
2023-08-11 Example copied from LUFA low-level keyboard demo.
2023-08-11 LUFA attempt, fails , probably problem with XMEGA devices support in LUFA.
2023-08-11 Ortho82 LUFA libary based trial. (#14)
    * Documentation update with photos of assembled keyboard.
    * Correct the formatting.
    * Example copied from LUFA low-level keyboard demo.
    * LUFA attempt, fails , probably problem with XMEGA devices support in LUFA.
2023-08-11 Clean up for CircuitPython code.
2023-08-11 Working right half of the keyboard.
2023-08-11 Sort the second half of the keyboard, left side in this case.
2023-08-12 Restructure Keycode maps to avoid conditionals, clean logic to work as per USB connected half.
2023-08-12 Add event decoding and processing for other half not connected to USB.
2023-08-13 Correct the layout with British PC keycodes.
2023-08-13 If GP16 is not pulled low,hide the circuitpython drive.
2023-08-16 Place keyboard keymap in a separate script, set board status flags.
2023-08-16 Setup matrix scanner and display the events.
2023-08-16 Issue persists, tested on macOS.
2024-11-12 Redoing firmware initial commit.
2024-11-13 Converted to Atmel Start based, keyboard scan and UART working.
2024-11-14 Keyboard scanning and mapping, sending data on UARTD1
    PD6, PD7 are RX, TX
2024-11-14 Detect all keys reproducibly, but sends multiple keystrokes.
    Need to do key down and up state machine.
2024-11-14 TODO for next task.
2024-11-16 Key events pressed and released.
    Need to fix sending pressed multiple times.
2024-11-16 Move versions file inside project
2024-11-16 Rename to more relevant to its behaviour, Keys Type
2024-11-16 Pre-build event to increment build timestamp, does not work in IDE
2024-11-16 Pressed and Released events work well.
2024-11-16 Move LED toggle to each event.
2024-11-16 Read key event from other half of keyboard.
2024-11-16 IRQ driven UART for receving to have buffer.
2024-11-17 Initial commit, led blink.
2024-11-17 Try sending Windows key, does not work.
2024-11-17 115200 baud
2024-11-22 Rename UART for easy identification, baud rate to match CH9328
2024-11-25 Add keycodes map for LEFT HALF
2024-11-25 hid keys to hold modifier and keys
2024-11-25 Rehearsing CH9328 via USB UART Cable.
2024-11-25 ignore compiled python bytecode
2024-11-25 a test workflow for xmega32u4 keyboard
2024-11-26 final test workflow
2024-11-27 initial value TX(PE3) to high, avoid sending 0xFF on reset
2024-11-27 Key press and release working, both UART polled, no 0xFF on reset.
2024-11-28 update keys human readable identifier to 2 char long
2024-11-28 simplify main loop for clean code
2024-11-28 Remove unused variables
2024-11-29 Fix bug: modifier should be detected by actual key id not by code.
    Modifier and non-modifier share keycode. Therefore determining whether a key is a modifier or not should be based on key id on the keyboard layout.
2024-11-29 Conditional output hex bytes for CH9823 or chars for terminal.
2024-11-29 Correct the UART to CH9823
2024-11-30 update to circuitpython 9.x, including libs
2024-11-30 Both left and right halves done.
2024-11-30 Fix processing of right half data and formatting to USB HID Processor.
2024-11-30 Try to fix
2024-11-30 Circuit python HID USB Keyboard middle device
2024-11-30 Increase RX buffer size, Round Robin Scheduling for Interrupts
2024-11-30 Real fix with decoding right side, Round Robin Interrupts for two USARTs were essential.
2024-12-01 USB 48 MHz, regenerate config.
2024-12-01 Test to check working
2024-12-01 Swap the main side to right as it has better place for Xiao SAMD21
2024-12-06 Ignore KiCad lock file.
2024-12-08 Only enable keyboard HID on boot, modifier layer keys
2024-12-08 add functio keys to modifier layer for right half
2024-12-08 (macNN-ioexp): basic working right half
2024-12-15 Fix duplicate matching mod key and real key
2024-12-17 first commit with Keyboard USBD Descriptor
2024-12-17 Correct spacing and kb2040 try.
2024-12-17 New trial with 66 keys layout.
2024-12-30 Initial commit for stagy66 firmware with STM32F072
2024-12-30 use USART1 for debug, usb descriptor and packet size
2024-12-30 run debug without halt at main
2024-12-30 remove connection to external CN3 on discovery board
2024-12-30 correct format specifier for unsigned long (uint32_t)
2024-12-30 CircuitPython with nRF52840 ItsyBitsy board
2024-12-30 Functioning left-half of BLE Keyboard.
2026-04-26 feat: basic working with defmt rtt logging
2026-04-26 feat: get the keypad switches matrix status

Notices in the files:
MacSplitNN/MacSplit60.kicad_pcb:
Copyright 2023, 125 Systems.
Ortho62Unified/Ortho62Unified.kicad_pcb:
Copyright 2022, 125 Systems.
